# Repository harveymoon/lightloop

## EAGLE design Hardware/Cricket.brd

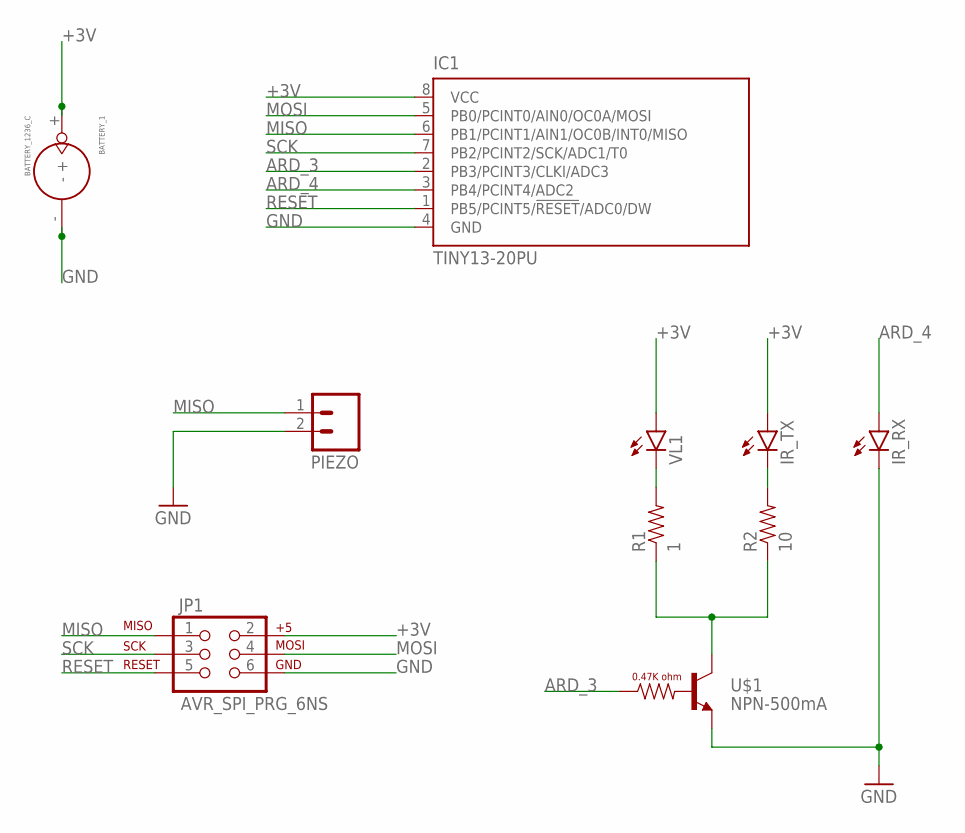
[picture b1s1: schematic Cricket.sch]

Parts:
BATTERY_1: BATTERY_1236_C
IC1: TINY13-20PU; DIL08
IR_RX: LED5MM; MPN SFH206K
IR_TX: LED5MM; MPN OP293B
JP1: AVR_SPI_PRG_6NS; 2X3-NS
PIEZO: M02PTH; 1X02
R1: 1; 1206
R2: 10; 1206
U$1: NPN-500mA; SOT23-3
VL1: LED5MM; MPN OP293B

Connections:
+3V: BATTERY_1.+, IC1.8 (VCC), IR_TX.A, JP1.2, VL1.A
ARD_3: IC1.2 (PB3/PCINT3/CLKI/ADC3), U$1.1 (B)
ARD_4: IC1.3 (PB4/PCINT4/ADC2), IR_RX.A
GND: BATTERY_1.-, IC1.4 (GND), IR_RX.K (C), JP1.6, PIEZO.2, U$1.2 (E)
MISO: IC1.6 (PB1/PCINT1/AIN1/OC0B/INT0/MISO), JP1.1, PIEZO.1
MOSI: IC1.5 (PB0/PCINT0/AIN0/OC0A/MOSI), JP1.4
unnamed: R1.2, VL1.K (C)
unnamed: IR_TX.K (C), R2.2
unnamed: R1.1, R2.1, U$1.3 (C)
RESET: IC1.1 (PB5/PCINT5/!RESET!/ADC0/DW), JP1.5
SCK: IC1.7 (PB2/PCINT2/SCK/ADC1/T0), JP1.3

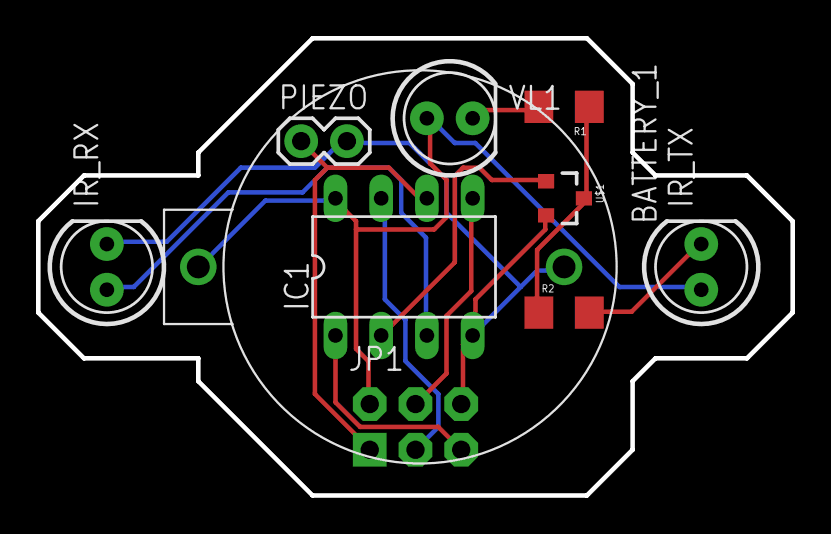
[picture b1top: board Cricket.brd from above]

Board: 2 copper layers, 41.9 x 25.4 mm, 10 parts (0 on the bottom side), 11 nets.

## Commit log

2015-09-25 Initial Commit. Firmware loaded on first two ATTiny85s
2015-09-25 Working code. Adding sleep.
2015-09-26 v2 Firmware used on final day
2015-09-28 Twitter Python Script + Puck Arduino Code + Sleep on Tinys
2015-09-29 Added PCB

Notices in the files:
parts and their libraries:
SparkFun-Connectors: Licensing: Creative Commons ShareAlike 4.0 International - https://creativecommons.org/licenses/by-sa/4.0
